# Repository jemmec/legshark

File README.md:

# legshark

An open source 60% (15 by 5) ortholinear keyboard designed with both flexability and familiarity in mind.

- Highly customizable 60% ortho layout
- "Plateless" o-ring mounting
- 3D printable case
- [UDB](https://github.com/Unified-Daughterboard/) Support

### Layout

The PCB supports many different layout options for the bottom row, embracing `1u` keys but also with some left and right `1.5u` modifier options.

The board also supports use of `2u` keys in the usual `TAB`, `LSHIFT`, `DELETE`, and `ENTER` locations to maintain familiarity and speed with these often used modifiers.

### PCB

> NOTE: It is recommended to use screw-in stabilizers (yes they work with o-ring) due to clip-ins sometimes slipping between the three holes in the bottom row. I have slightly reduced the clip-in hole size which has mitigated the issue, but made them quite hard to push in.

>_These images may not be up-to-date._

Supports the [Unified Daughterboard](https://github.com/Unified-Daughterboard/).

### Mounting Styles

Supports a unique "plateless" o-ring mounting style. The PCB also has through-holes for plate mounting should that be preferred.

#### "Plateless" o-ring plate

The "plateless" o-ring mounting style lets you enjoy the unique characteristics and sound of a platless + o-ring board with the added benefit of being able to remove/change the plate after soldering in the switches.

The printable plate files can be found in `./stls`. There are two files, one for `1.5u` spaced switches (pictured) and one for the `1u` spaced switches. Only the left side plate is supplied, you will need to vertically mirror the file in your slicer to print the right side. The optimal printing orientation is upside-down.

A standard 60% o-ring (OD 180-190mm) with a diameter of 2.5-3.5mm will work. 

>NOTE: If you intend to use a layout with the `2u` SHIFT or DELETE keys these plates may need modified in order to fit the stabs.

### Case

A 3D printable case designed around the "plateless" o-ring mounting system. It's a unibody design with a daughterboard cutout and recessed holes for 12mm rubber feet. The daughterboard is screwed into M2 threaded inserts.

Files for printing the case can be found in `./stls`. The print has been split into two parts, since it is too large for standard-sized printer volumes. The two halves are designed to be glued together using key and slot guides for alignment and added strength. The optimal printing orientation is vertically with the case-sides facing down.

>NOTE: I recommend using superglue to bond the two halves together.
>1) Glue all three keys into the slots of one of the halves. 
>2) Add glue along the mating surface and in the slots of the other half. 
>3) Carefully slide the two halves together using the keys and slots a guide. 
>4) Clamp the halves together and let the glue dry for 10-20 minutes.

### QMK

There is only one keymap avaliable for the keyboard currently. This keyboard has not been merged into the qmk repo yet. The firmware will need to be compiled and uploaded locally using [QMK](https://qmk.fm/). 

Copy `./qmk/keyboards` into your `/qmk_firmware` folder then run the following command to compile the firmware:
```
qmk compile -kb legshark/rev2 -km default
```

>NOTE: You will need to modify the keymaps to support different layouts!

### Keyboard Layout Editor:

```
[{x:2,c:"#c9a6de",t:"#383838",st:"KS-3-Tea",a:3,f:4},"ESC\n\n\n\n\n0\n\n\n\n\n\n0",{c:"#cccccc",a:1},"~\n`\n\n\n\n1\n\n\n\n\n\n0","!\n1\n\n\n\n2\n\n\n\n\n\n0","@\n2\n\n\n\n3\n\n\n\n\n\n0","#\n3\n\n\n\n4\n\n\n\n\n\n0","$\n4\n\n\n\n5\n\n\n\n\n\n0","%\n5\n\n\n\n6\n\n\n\n\n\n0","^\n6\n\n\n\n7\n\n\n\n\n\n0","&\n7\n\n\n\n8\n\n\n\n\n\n0","*\n8\n\n\n\n9\n\n\n\n\n\n0","(\n9\n\n\n\n10\n\n\n\n\n\n0",")\n0\n\n\n\n11\n\n\n\n\n\n0","_\n-\n\n\n\n12\n\n\n\n\n\n0","+\n=\n\n\n\n13\n\n\n\n\n\n0",{c:"#c9a6de",a:3},"DEL\n\n\n\n\n14\n\n\n\n\n\n0",{w:2},"DELETE\n\n\n\n2u\n0 14"],
[{w:2},"TAB\n\n\n\n2u\n1 0","\n\n\n\n\n0\n\n\n\n\n\n1","\n\n\n\n\n1\n\n\n\n\n\n1",{c:"#cccccc",f:6},"Q\n\n\n\n\n2\n\n\n\n\n\n1","W\n\n\n\n\n3\n\n\n\n\n\n1","E\n\n\n\n\n4\n\n\n\n\n\n1","R\n\n\n\n\n5\n\n\n\n\n\n1","T\n\n\n\n\n6\n\n\n\n\n\n1","Y\n\n\n\n\n7\n\n\n\n\n\n1","U\n\n\n\n\n8\n\n\n\n\n\n1","I\n\n\n\n\n9\n\n\n\n\n\n1","O\n\n\n\n\n10\n\n\n\n\n\n1","P\n\n\n\n\n11\n\n\n\n\n\n1",{a:1,f:4},"{\n[\n\n\n\n12\n\n\n\n\n\n1","}\n]\n\n\n\n13\n\n\n\n\n\n1","|\n\\\n\n\n\n14\n\n\n\n\n\n1"],
[{x:2,c:"#c9a6de",a:3},"CAPS\n\n\n\n\n0\n\n\n\n\n\n2","FN\n\n\n\n\n1\n\n\n\n\n\n2",{c:"#cccccc",f:6},"A\n\n\n\n\n2\n\n\n\n\n\n2","S\n\n\n\n\n3\n\n\n\n\n\n2","D\n\n\n\n\n4\n\n\n\n\n\n2",{a:1},"\n_\n\n\n\n5\nF\n\n\n\n\n2",{a:3},"G\n\n\n\n\n6\n\n\n\n\n\n2","H\n\n\n\n\n7\n\n\n\n\n\n2",{a:1},"\n_\n\n\n\n8\nJ\n\n\n\n\n2",{a:3},"K\n\n\n\n\n9\n\n\n\n\n\n2","L\n\n\n\n\n10\n\n\n\n\n\n2",{a:1,f:4},":\n;\n\n\n\n11\n\n\n\n\n\n2","\"\n'\n\n\n\n12\n\n\n\n\n\n2",{c:"#c9a6de",a:3},"\n\n\n\n\n13\n\n\n\n\n\n2","\n\n\n\n\n14\n\n\n\n\n\n2",{w:2},"ENTER\n\n\n\n2u\n2 14"],
[{w:2},"SHIFT\n\n\n\n2u\n3 0","\n\n\n\n\n0\n\n\n\n\n\n3","\n\n\n\n\n1\n\n\n\n\n\n3",{c:"#cccccc",f:6},"Z\n\n\n\n\n2\n\n\n\n\n\n3","X\n\n\n\n\n3\n\n\n\n\n\n3","C\n\n\n\n\n4\n\n\n\n\n\n3","V\n\n\n\n\n5\n\n\n\n\n\n3","B\n\n\n\n\n6\n\n\n\n\n\n3","N\n\n\n\n\n7\n\n\n\n\n\n3","M\n\n\n\n\n8\n\n\n\n\n\n3",{a:1,f:4},"<\n,\n\n\n\n9\n\n\n\n\n\n3",">\n.\n\n\n\n10\n\n\n\n\n\n3","?\n/\n\n\n\n11\n\n\n\n\n\n3",{c:"#bf6060",a:3,f:9},"↑\n\n\n\n\n12\n\n\n\n\n\n3",{c:"#c9a6de",f:4},"\n\n\n\n\n13\n\n\n\n\n\n3","\n\n\n\n\n14\n\n\n\n\n\n3"],
[{x:3,c:"#73c985"},"LCTL\n\n\n\n\n1\n\n\n\n\n\n4","\n\n\n\n\n2\n\n\n\n\n\n4","LALT\n\n\n\n\n3\n\n\n\n\n\n4",{c:"#7acdff",sm:"alps"},"\n\n\n\n\n4\n\n\n\n\n\n4","\n\n\n\n\n5\n\n\n\n\n\n4","\n\n\n\n\n6\n\n\n\n\n\n4","\n\n\n\n\n7\n\n\n\n\n\n4","\n\n\n\n\n8\n\n\n\n\n\n4","\n\n\n\n\n9\n\n\n\n\n\n4","\n\n\n\n\n10\n\n\n\n\n\n4",{c:"#bf6060",f:9},"←\n\n\n\n\n11\n\n\n\n\n\n4","↓\n\n\n\n\n12\n\n\n\n\n\n4","→\n\n\n\n\n13\n\n\n\n\n\n4"],
[{x:3,c:"#73c985",f:4,w:1.5},"LCTL\n\n\n\n\n4 1","\n\n\n\n\n2\n\n\n\n\n\n4",{w:1.5},"LALT\n\n\n\n\n4 4",{x:1,c:"#7acdff",w:3},"\n\n\n\n3u\n4 7",{x:1,c:"#73c985",w:1.5},"RALT\n\n\n\n\n4 10","\n\n\n\n\n4 12",{w:1.5},"RCTL\n\n\n\n\n4 13"],
[{x:3,w:1.5},"LCTL\n\n\n\n\n4 1",{w:1.5},"\n\n\n\n\n4 3",{c:"#7acdff",w:3},"\n\n\n\n3u\n4 5",{x:1,w:3},"\n\n\n\n3u\n4 9",{c:"#73c985",w:1.5},"\n\n\n\n\n4 11",{w:1.5},"RCTL\n\n\n\n\n4 13"],
[{x:8,c:"#7acdff",w:2},"\n\n\n\n2u\n4 7",{w:2},"\n\n\n\n2u\n4 8"],
[{x:7,w:2},"\n\n\n\n2u\n4 6",{w:2},"\n\n\n\n2u\n4 7"],
[{x:7,w:3},"\n\n\n\n3u\n4 6"],
[{x:9,w:3},"\n\n\n\n3u\n4 8"],
[{x:6,w:7},"\n\n\n\n7u\n4 7"]
```
# Liability

This open source hardware is provided as is and can not be held accountable for any damages and/or liabilities caused as a result of whatever you intend to use it for.

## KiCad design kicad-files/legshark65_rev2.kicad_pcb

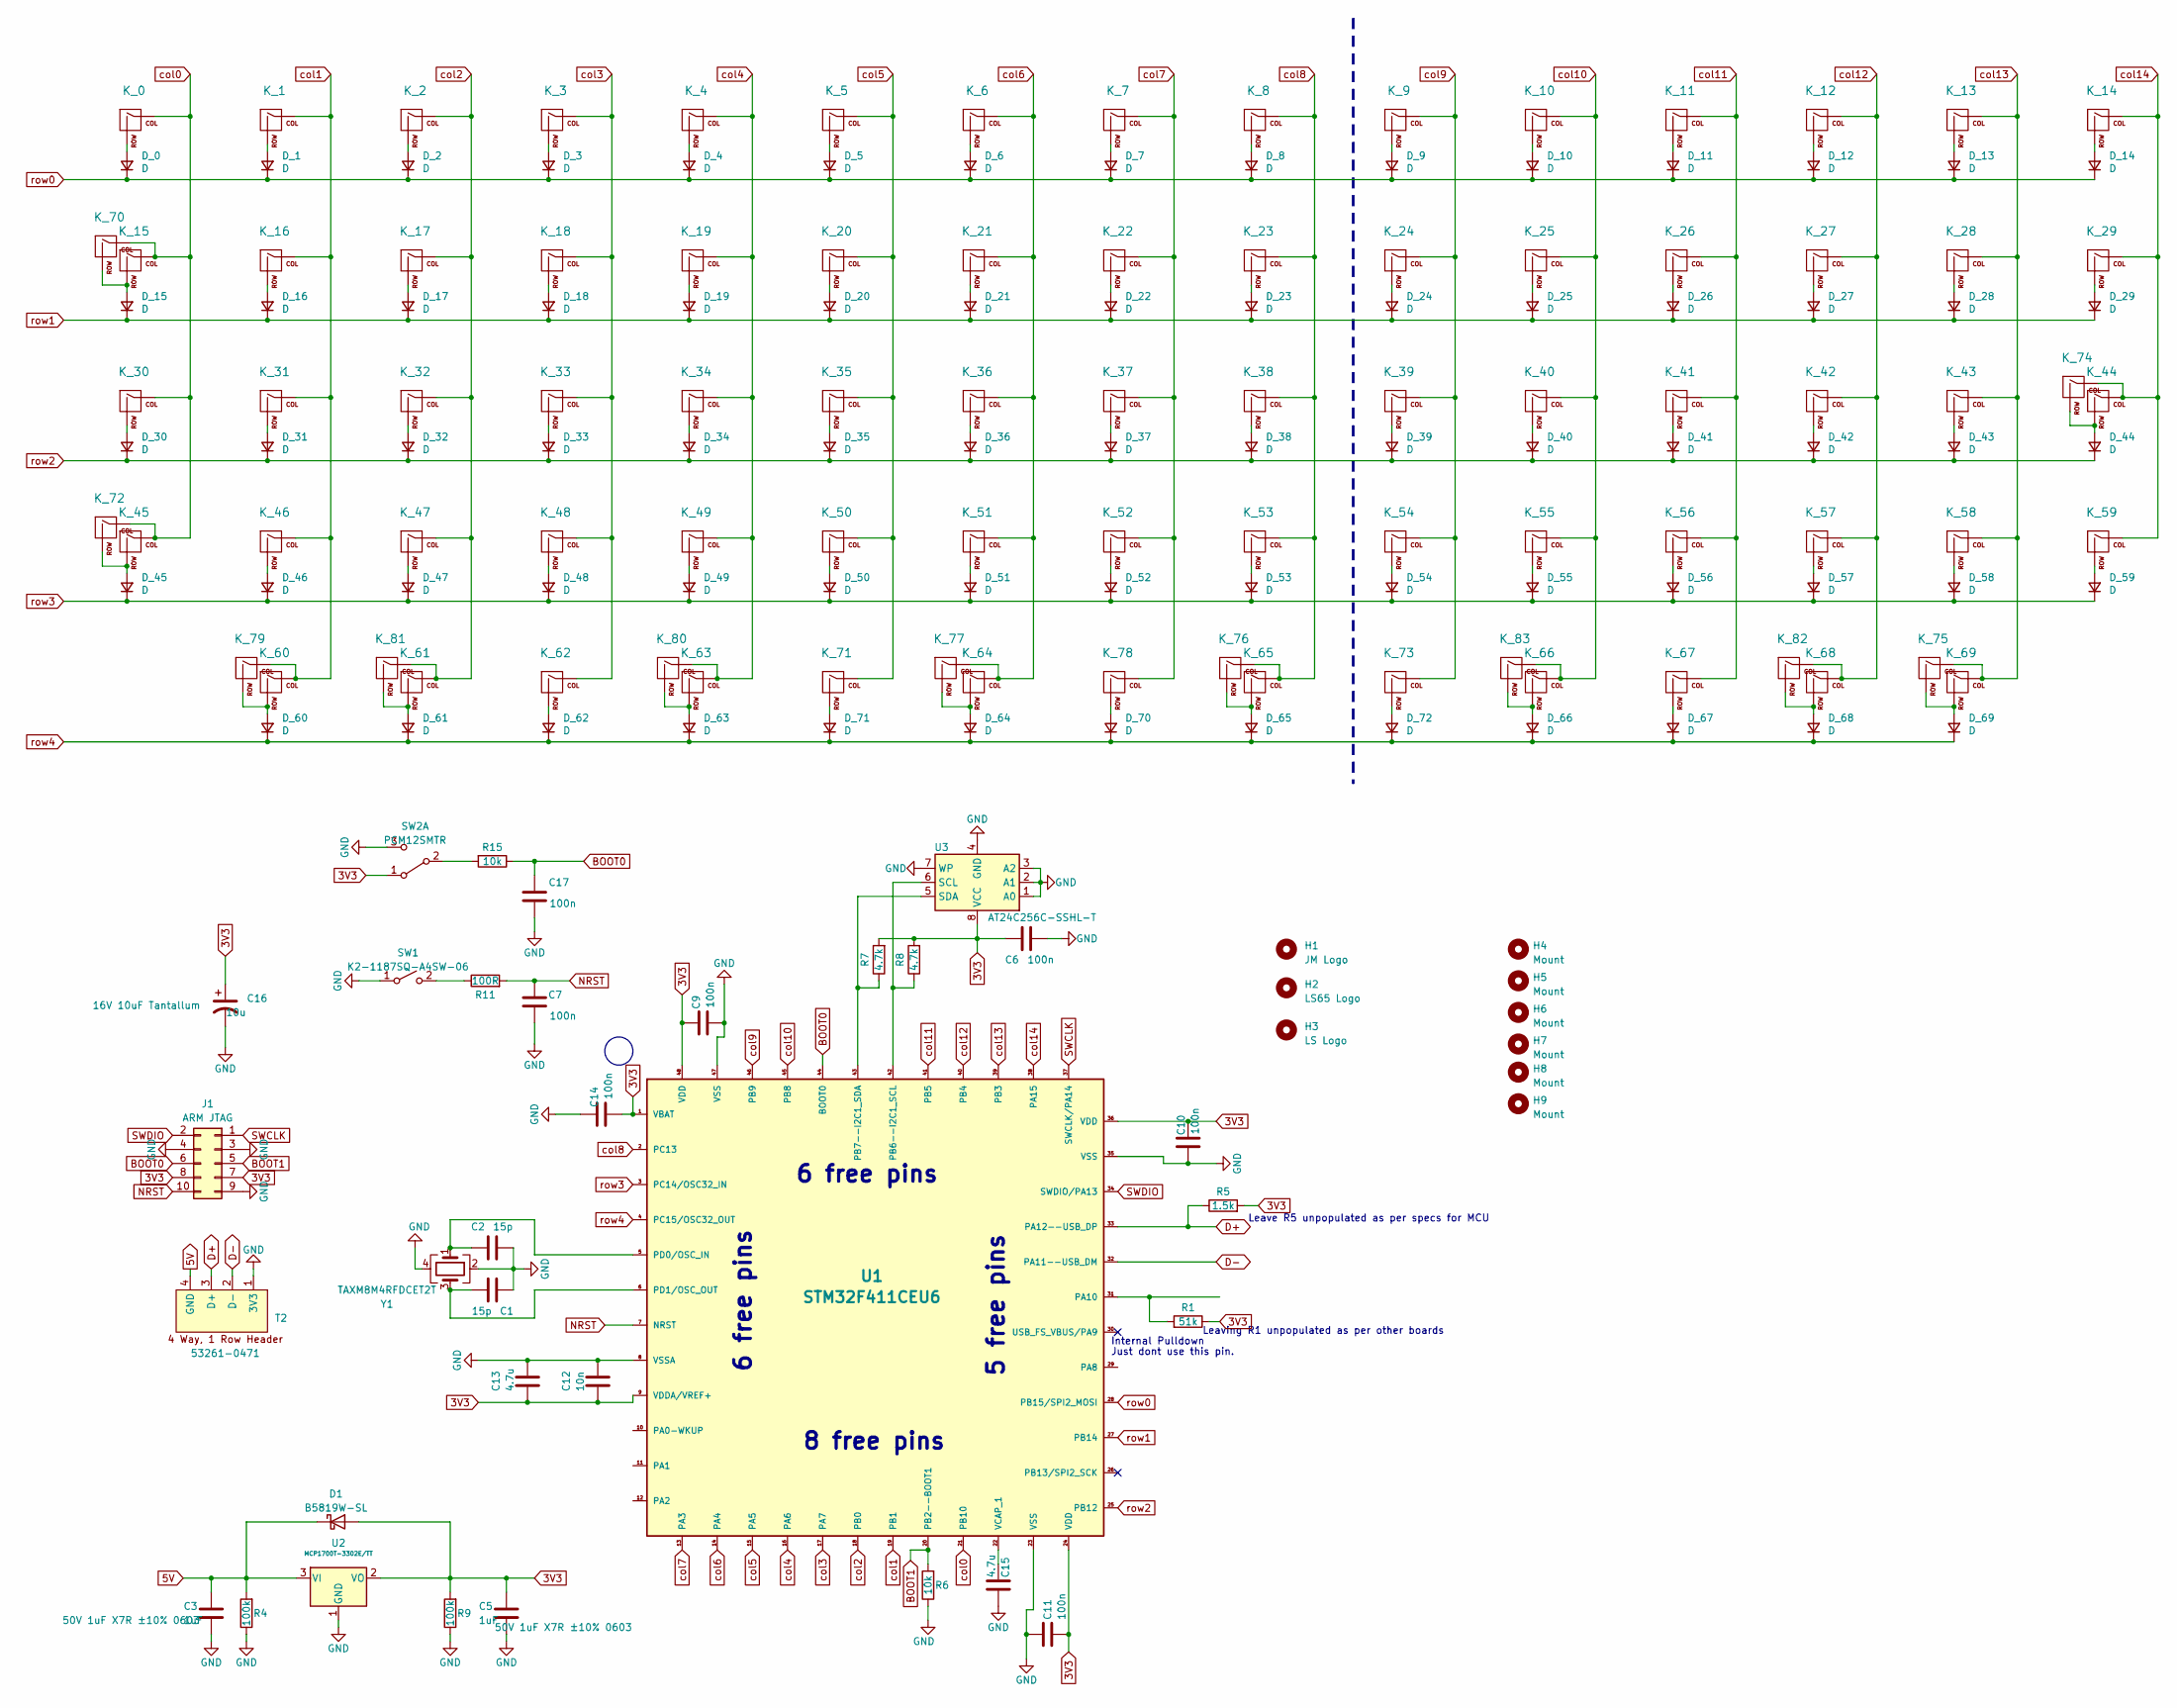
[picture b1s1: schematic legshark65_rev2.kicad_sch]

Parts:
C1, C2: 15p; C_0402_1005Metric_Pad0.74x0.62mm_HandSolder; Manufacturer Part Number CC0603JRNPO9BN150; LCSC Part C107037
C3, C5: 1uF; C_0402_1005Metric_Pad0.74x0.62mm_HandSolder; Manufacturer Part Number 0603B105K500NT
C6, C7, C9, C10, C11, C14, C17: 100n; C_0402_1005Metric_Pad0.74x0.62mm_HandSolder; Manufacturer Part Number CL10B104KB8NNNC; LCSC Part C1591
C12: 10n; C_0402_1005Metric_Pad0.74x0.62mm_HandSolder; Manufacturer Part Number CL10B103KB8NNNC; LCSC Part C1589
C13, C15: 4.7u; C_0402_1005Metric_Pad0.74x0.62mm_HandSolder; Manufacturer Part Number 0603X475M100NT; LCSC Part C108342
C16: 10u; CP_EIA-3216-10_Kemet-I_Pad1.58x1.35mm_HandSolder; Manufacturer Part Number TAJA106K016RNJ; LCSC Part C7171
D1: B5819W-SL; D_SOD-123
D_0, D_1, D_2, D_3, D_4, D_5, D_6, D_7, D_8, D_9, D_10, D_11, D_12, D_13, D_14, D_15, D_16, D_17, D_18, D_19, D_20, D_21, D_22, D_23, D_24, D_25, D_26, D_27, D_28, D_29, D_30, D_31, D_32, D_33, D_34, D_35, D_36, D_37, D_38, D_39, D_40, D_41, D_42, D_43, D_44, D_45, D_46, D_47, D_48, D_49, D_50, D_51, D_52, D_53, D_54, D_55, D_56, D_57, D_58, D_59, D_60, D_61, D_62, D_63, D_64, D_65, D_66, D_67, D_68, D_69, D_70, D_71, D_72: D; D_SOD-523
H1: JM Logo; jm_logo
H2: LS65 Logo; ls65_logo
H3: LS Logo; Legshark_Mask
H4, H5, H6, H7, H8, H9: Mount; MountingHole_3.2mm_M3_ISO14580
J1: ARM JTAG; PinHeader_2x5_P2.54mm_Vertical
K_0, K_1, K_2, K_3, K_4, K_5, K_6, K_7, K_8, K_9, K_10, K_11, K_12, K_13, K_14, K_15, K_16, K_17, K_18, K_19, K_20, K_21, K_22, K_23, K_24, K_25, K_26, K_27, K_28, K_29, K_30, K_31, K_32, K_33, K_34, K_35, K_36, K_37, K_38, K_39, K_40, K_41, K_42, K_43, K_44, K_45, K_46, K_47, K_48, K_49, K_50, K_51, K_52, K_53, K_54, K_55, K_56, K_57, K_58, K_59, K_60, K_61, K_62, K_63, K_66, K_67, K_68, K_69, K_71, K_73, K_81, K_82: KEYSW; MXOnly-1U-NoLED
K_64, K_76: KEYSW; MXOnly-2U-ReversedStabilizers-NoLED
K_65, K_77: KEYSW; MXOnly-3U-ReversedStabilizers-NoLED
K_70, K_72, K_74: KEYSW; MXOnly-2U-NoLED
K_75, K_79, K_80, K_83: KEYSW; MXOnly-1.5U-NoLED
K_78: KEYSW; Legshark_MXOnly-7U-3U-ReversedStabilizers-NoLED
R1: 51k; R_0402_1005Metric_Pad0.72x0.64mm_HandSolder
R4, R9: 100k; R_0402_1005Metric_Pad0.72x0.64mm_HandSolder
R5: 1.5k; R_0402_1005Metric_Pad0.72x0.64mm_HandSolder
R6, R15: 10k; R_0402_1005Metric_Pad0.72x0.64mm_HandSolder; Manufacturer Part Number 0603WAF1002T5E; LCSC Part C25804
R7, R8: 4.7k; R_0402_1005Metric_Pad0.72x0.64mm_HandSolder; Manufacturer Part Number 0603WAF4701T5E; LCSC Part C23162
R11: 100R; R_0402_1005Metric_Pad0.72x0.64mm_HandSolder; Manufacturer Part Number 0603WAF1000T5E; LCSC Part C22775
SW1: K2-1187SQ-A4SW-06; Manufacturer Part Number K2-1187SQ-A4SW-06; LCSC Part C92584
SW2: PCM12SMTR; Surface Mount Slide Switch SPDT; Manufacturer Part Number PCM12SMTR; LCSC Part C221841
T2: 53261-0471; Molex, PicoBlade, 53261, 4 Way, 1 Row, Right Angle PCB Head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
U1: STM32F411CEU6; STM_UFQFPN-48_LQFP-48-1EP_7x7mm_P0.5mm_HandSoldering; Manufacturer Part Number STM32F411; LCSC Part C60420
U2: MCP1700T-3302E/TT; SOT-23; Manufacturer Part Number MCP1700T-3302E/TT
U3: AT24C256C-SSHL-T; SOIC-8; Manufacturer Part Number AT24C256C-SSHL-T; LCSC Part C6482
Y1: TAXM8M4RFDCET2T; Crystal_SMD_3225-4Pin_3.2x2.5mm; Manufacturer Part Number TAXM8M4RFDCET2T; LCSC Part C403948

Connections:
3V3: C5.1, C6.1, C9.2, C10.2, C11.2, C12.2, C13.2, C14.1, C16.1, D1.2 (A), J1.7, J1.8, R1.1, R5.2, R7.2, R8.2, R9.2, SW2.1 (A), U1.1 (VBAT), U1.9 (VDDA/VREF+), U1.24 (VDD), U1.36 (VDD), U1.48 (VDD), U2.2 (VO), U3.8 (VCC)
5V: C3.1, D1.1 (K), R4.2, T2.4 (GND), U2.3 (VI)
BOOT0: C17.2, J1.6, R15.1, U1.44 (BOOT0)
BOOT1: J1.5, R6.2, U1.20 (PB2--BOOT1)
D+: R5.1, T2.3 (D+), U1.33 (PA12--USB_DP)
D-: T2.2 (D-), U1.32 (PA11--USB_DM)
GND: C1.1, C2.2, C3.2, C5.2, C6.2, C7.1, C9.1, C10.1, C11.1, C12.1, C13.1, C14.2, C15.2, C16.2, C17.1, J1.3, J1.4, J1.9, R4.1, R6.1, R9.1, SW1.1 (A), SW2.3 (C), T2.1 (3V3), U1.8 (VSSA), U1.23 (VSS), U1.35 (VSS), U1.47 (VSS), U2.1 (GND), U3.1 (A0), U3.2 (A1), U3.3 (A2), U3.4 (GND), U3.7 (WP), Y1.2, Y1.4
NRST: C7.2, J1.10, R11.2, U1.7 (NRST)
unnamed: D_0.2 (A), K_0.2 (ROW)
unnamed: D_1.2 (A), K_1.2 (ROW)
unnamed: D_2.2 (A), K_2.2 (ROW)
unnamed: D_3.2 (A), K_3.2 (ROW)
unnamed: D_4.2 (A), K_4.2 (ROW)
unnamed: D_5.2 (A), K_5.2 (ROW)
unnamed: D_6.2 (A), K_6.2 (ROW)
unnamed: D_7.2 (A), K_7.2 (ROW)
unnamed: D_8.2 (A), K_8.2 (ROW)
unnamed: D_9.2 (A), K_9.2 (ROW)
unnamed: D_10.2 (A), K_10.2 (ROW)
unnamed: D_11.2 (A), K_11.2 (ROW)
unnamed: D_12.2 (A), K_12.2 (ROW)
unnamed: D_13.2 (A), K_13.2 (ROW)
unnamed: D_14.2 (A), K_14.2 (ROW)
unnamed: D_15.2 (A), K_15.2 (ROW), K_70.2 (ROW)
unnamed: D_16.2 (A), K_16.2 (ROW)
unnamed: D_17.2 (A), K_17.2 (ROW)
unnamed: D_18.2 (A), K_18.2 (ROW)
unnamed: D_19.2 (A), K_19.2 (ROW)
unnamed: D_20.2 (A), K_20.2 (ROW)
unnamed: D_21.2 (A), K_21.2 (ROW)
unnamed: D_22.2 (A), K_22.2 (ROW)
unnamed: D_23.2 (A), K_23.2 (ROW)
unnamed: D_24.2 (A), K_24.2 (ROW)
unnamed: D_25.2 (A), K_25.2 (ROW)
unnamed: D_26.2 (A), K_26.2 (ROW)
unnamed: D_27.2 (A), K_27.2 (ROW)
unnamed: D_28.2 (A), K_28.2 (ROW)
unnamed: D_29.2 (A), K_29.2 (ROW)
unnamed: D_30.2 (A), K_30.2 (ROW)
unnamed: D_31.2 (A), K_31.2 (ROW)
unnamed: D_32.2 (A), K_32.2 (ROW)
unnamed: D_33.2 (A), K_33.2 (ROW)
unnamed: D_34.2 (A), K_34.2 (ROW)
unnamed: D_35.2 (A), K_35.2 (ROW)
unnamed: D_36.2 (A), K_36.2 (ROW)
unnamed: D_37.2 (A), K_37.2 (ROW)
unnamed: D_38.2 (A), K_38.2 (ROW)
unnamed: D_39.2 (A), K_39.2 (ROW)
unnamed: D_40.2 (A), K_40.2 (ROW)
unnamed: D_41.2 (A), K_41.2 (ROW)
unnamed: D_42.2 (A), K_42.2 (ROW)
unnamed: D_43.2 (A), K_43.2 (ROW)
unnamed: D_44.2 (A), K_44.2 (ROW), K_74.2 (ROW)
unnamed: D_45.2 (A), K_45.2 (ROW), K_72.2 (ROW)
unnamed: D_46.2 (A), K_46.2 (ROW)
unnamed: D_47.2 (A), K_47.2 (ROW)
unnamed: D_48.2 (A), K_48.2 (ROW)
unnamed: D_49.2 (A), K_49.2 (ROW)
unnamed: D_50.2 (A), K_50.2 (ROW)
unnamed: D_51.2 (A), K_51.2 (ROW)
unnamed: D_52.2 (A), K_52.2 (ROW)
unnamed: D_53.2 (A), K_53.2 (ROW)
unnamed: D_54.2 (A), K_54.2 (ROW)
unnamed: D_55.2 (A), K_55.2 (ROW)
unnamed: D_56.2 (A), K_56.2 (ROW)
unnamed: D_57.2 (A), K_57.2 (ROW)
unnamed: D_58.2 (A), K_58.2 (ROW)
unnamed: D_59.2 (A), K_59.2 (ROW)
unnamed: D_60.2 (A), K_60.2 (ROW), K_79.2 (ROW)
unnamed: D_61.2 (A), K_61.2 (ROW), K_81.2 (ROW)
unnamed: D_62.2 (A), K_62.2 (ROW)
unnamed: D_63.2 (A), K_63.2 (ROW), K_80.2 (ROW)
unnamed: D_64.2 (A), K_64.2 (ROW), K_77.2 (ROW)
unnamed: D_65.2 (A), K_65.2 (ROW), K_76.2 (ROW)
unnamed: D_66.2 (A), K_66.2 (ROW), K_83.2 (ROW)
unnamed: D_67.2 (A), K_67.2 (ROW)
unnamed: D_68.2 (A), K_68.2 (ROW), K_82.2 (ROW)
unnamed: D_69.2 (A), K_69.2 (ROW), K_75.2 (ROW)
unnamed: D_70.2 (A), K_78.2 (ROW)
unnamed: D_71.2 (A), K_71.2 (ROW)
unnamed: D_72.2 (A), K_73.2 (ROW)
unnamed: R11.1, SW1.2 (B)
unnamed: R15.2, SW2.2 (B)
unnamed: R1.2, U1.31 (PA10)
unnamed: R8.1, U1.42 (PB6--I2C1_SCL), U3.6 (SCL)
unnamed: R7.1, U1.43 (PB7--I2C1_SDA), U3.5 (SDA)
unnamed: C2.1, U1.5 (PD0/OSC_IN), Y1.1
unnamed: C1.2, U1.6 (PD1/OSC_OUT), Y1.3
unnamed: C15.1, U1.22 (VCAP_1)
SWCLK: J1.1, U1.37 (SWCLK/PA14)
SWDIO: J1.2, U1.34 (SWDIO/PA13)
col0: K_0.1 (COL), K_15.1 (COL), K_30.1 (COL), K_45.1 (COL), K_70.1 (COL), K_72.1 (COL), U1.21 (PB10)
col1: K_1.1 (COL), K_16.1 (COL), K_31.1 (COL), K_46.1 (COL), K_60.1 (COL), K_79.1 (COL), U1.19 (PB1)
col2: K_2.1 (COL), K_17.1 (COL), K_32.1 (COL), K_47.1 (COL), K_61.1 (COL), K_81.1 (COL), U1.18 (PB0)
col3: K_3.1 (COL), K_18.1 (COL), K_33.1 (COL), K_48.1 (COL), K_62.1 (COL), U1.17 (PA7)
col4: K_4.1 (COL), K_19.1 (COL), K_34.1 (COL), K_49.1 (COL), K_63.1 (COL), K_80.1 (COL), U1.16 (PA6)
col5: K_5.1 (COL), K_20.1 (COL), K_35.1 (COL), K_50.1 (COL), K_71.1 (COL), U1.15 (PA5)
col6: K_6.1 (COL), K_21.1 (COL), K_36.1 (COL), K_51.1 (COL), K_64.1 (COL), K_77.1 (COL), U1.14 (PA4)
col7: K_7.1 (COL), K_22.1 (COL), K_37.1 (COL), K_52.1 (COL), K_78.1 (COL), U1.13 (PA3)
col8: K_8.1 (COL), K_23.1 (COL), K_38.1 (COL), K_53.1 (COL), K_65.1 (COL), K_76.1 (COL), U1.2 (PC13)
col9: K_9.1 (COL), K_24.1 (COL), K_39.1 (COL), K_54.1 (COL), K_73.1 (COL), U1.46 (PB9)
col10: K_10.1 (COL), K_25.1 (COL), K_40.1 (COL), K_55.1 (COL), K_66.1 (COL), K_83.1 (COL), U1.45 (PB8)
col11: K_11.1 (COL), K_26.1 (COL), K_41.1 (COL), K_56.1 (COL), K_67.1 (COL), U1.41 (PB5)
col12: K_12.1 (COL), K_27.1 (COL), K_42.1 (COL), K_57.1 (COL), K_68.1 (COL), K_82.1 (COL), U1.40 (PB4)
col13: K_13.1 (COL), K_28.1 (COL), K_43.1 (COL), K_58.1 (COL), K_69.1 (COL), K_75.1 (COL), U1.39 (PB3)
col14: K_14.1 (COL), K_29.1 (COL), K_44.1 (COL), K_59.1 (COL), K_74.1 (COL), U1.38 (PA15)
row0: D_0.1 (K), D_1.1 (K), D_2.1 (K), D_3.1 (K), D_4.1 (K), D_5.1 (K), D_6.1 (K), D_7.1 (K), D_8.1 (K), D_9.1 (K), D_10.1 (K), D_11.1 (K), D_12.1 (K), D_13.1 (K), D_14.1 (K), U1.28 (PB15/SPI2_MOSI)
row1: D_15.1 (K), D_16.1 (K), D_17.1 (K), D_18.1 (K), D_19.1 (K), D_20.1 (K), D_21.1 (K), D_22.1 (K), D_23.1 (K), D_24.1 (K), D_25.1 (K), D_26.1 (K), D_27.1 (K), D_28.1 (K), D_29.1 (K), U1.27 (PB14)
row2: D_30.1 (K), D_31.1 (K), D_32.1 (K), D_33.1 (K), D_34.1 (K), D_35.1 (K), D_36.1 (K), D_37.1 (K), D_38.1 (K), D_39.1 (K), D_40.1 (K), D_41.1 (K), D_42.1 (K), D_43.1 (K), D_44.1 (K), U1.25 (PB12)
row3: D_45.1 (K), D_46.1 (K), D_47.1 (K), D_48.1 (K), D_49.1 (K), D_50.1 (K), D_51.1 (K), D_52.1 (K), D_53.1 (K), D_54.1 (K), D_55.1 (K), D_56.1 (K), D_57.1 (K), D_58.1 (K), D_59.1 (K), U1.3 (PC14/OSC32_IN)
row4: D_60.1 (K), D_61.1 (K), D_62.1 (K), D_63.1 (K), D_64.1 (K), D_65.1 (K), D_66.1 (K), D_67.1 (K), D_68.1 (K), D_69.1 (K), D_70.1 (K), D_71.1 (K), D_72.1 (K), U1.4 (PC15/OSC32_OUT)

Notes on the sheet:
6 free pins
5 free pins
Leave R5 unpopulated as per specs for MCU
Just dont use this pin.
Leaving R1 unpopulated as per other boards
8 free pins
Internal Pulldown

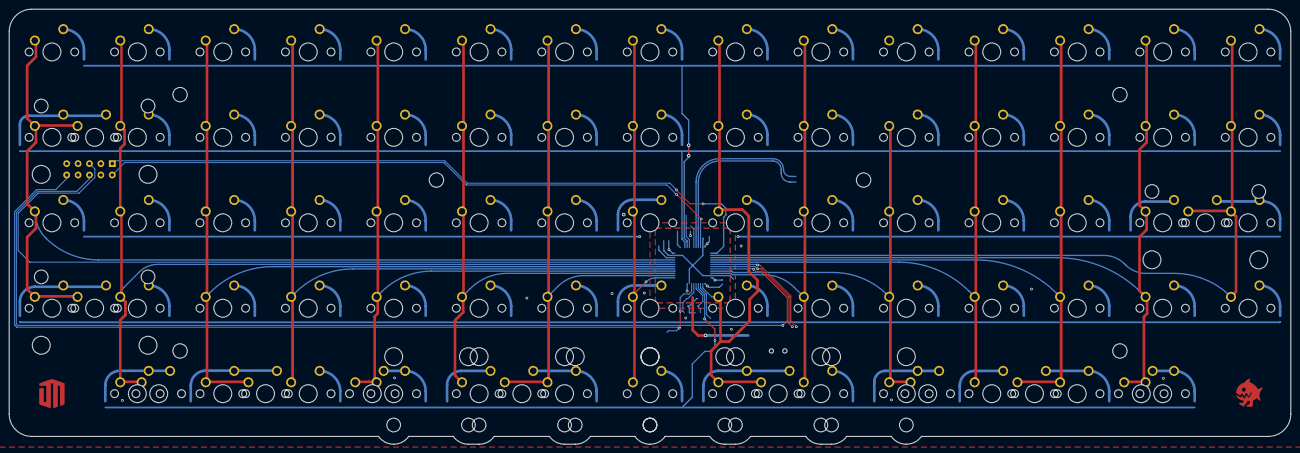
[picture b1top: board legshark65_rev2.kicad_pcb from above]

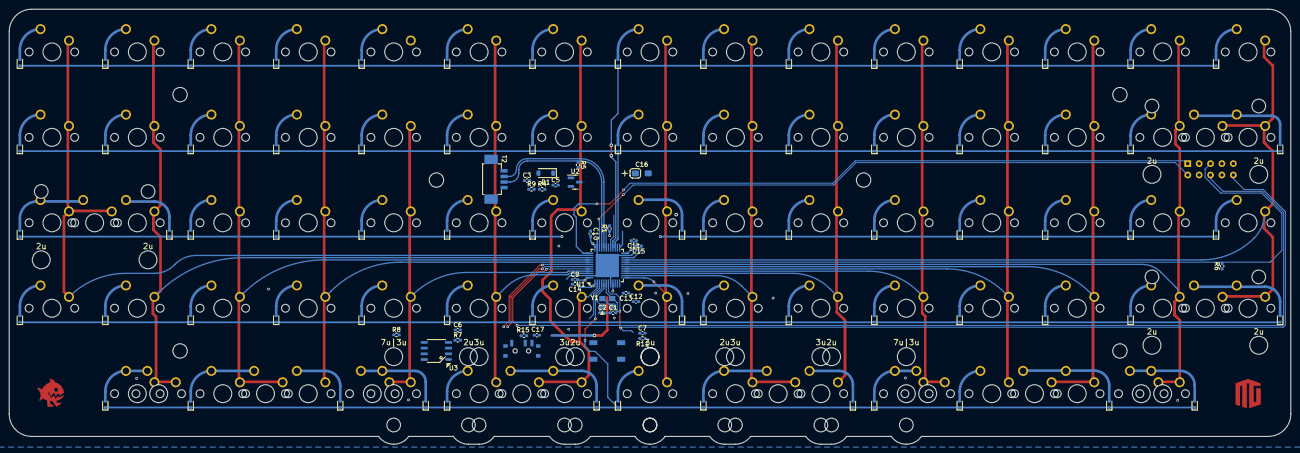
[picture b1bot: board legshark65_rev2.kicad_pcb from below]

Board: 2 copper layers, 285.8 x 97.0 mm, 199 parts (105 on the bottom side), 111 nets.

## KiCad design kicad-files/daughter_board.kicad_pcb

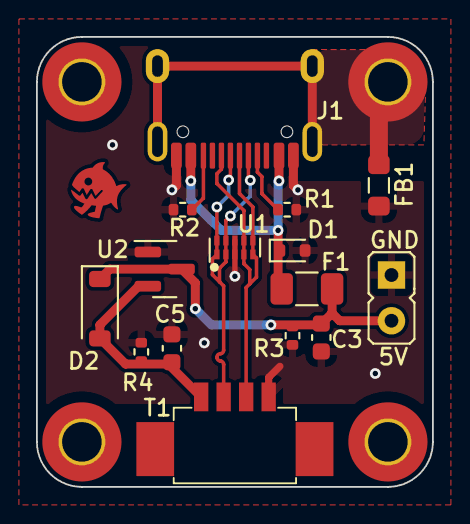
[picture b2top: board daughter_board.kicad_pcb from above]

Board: 2 copper layers, 22.0 x 25.0 mm, 20 parts (0 on the bottom side), 9 nets.

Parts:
C3, C5: 1uF; C_0603_1608Metric
D1: ESD5Z5V0; D_SOD-523
D2: B5819W-SL; D_SOD-123
F1: SMD0805-050-16V; Fuse_1206_3216Metric
FB1: GZ2012D601TF; L_0805_2012Metric_Pad1.05x1.20mm_HandSolder
H1: LegSharkLogo; Legshark_Small_Mask
J1: TYPE-C-31-M-12
J2: Conn_01x02; PinHeader_1x2_P2.54mm_Vertical
MH1, MH3, MH4: Mount-M2; MountingHole_2.2mm_M2_Pad_TopOnly
MH2: Mount-M2; MountingHole_2.2mm_M2_Pad_TopBottom
R1, R2: 5.1k; R_0402_1005Metric
R3, R4: 100k; R_0402_1005Metric
T1: 53261-0471; Molex, PicoBlade, 53261, 4 Way, 1 Row, Right Angle PCB Head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
U1: TPD4E05U06DQAR; USON-10_2.5x1.0mm_P0.5mm
U2: MCP1700T-3302E/TT; SOT-23

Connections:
3V3: C5.1, D2.2 (A), R4.2, T1.1 (3V3), U2.2 (VO)
5V: C3.1, D2.1 (K), F1.2, J2.2, R3.2, U2.3 (VI)
D+: J1.A6 (D+), J1.B6 (D+), T1.3 (D-), U1.4 (D2+), U1.5 (D2-), U1.6 (NC), U1.7 (NC)
D-: J1.A7 (D-), J1.B7 (D-), T1.2 (D+), U1.1 (IO1), U1.2 (IO2), U1.9 (NC), U1.10 (NC)
GND: C3.2, C5.2, D1.2 (A2), FB1.2, J1.A1 (GND), J1.B1 (GND), J2.1, R1.2, R2.2, R3.1, R4.1, T1.4 (GND), U1.3 (GND), U1.8 (GND), U2.1 (GND)
GNDPWR: FB1.1, J1.S (SHIELD), MH2.1
unnamed: J1.A5 (CC1), R1.1
unnamed: J1.B5 (CC2), R2.1
VBUS: D1.1 (A1), F1.1, J1.A4 (VBUS), J1.B4 (VBUS)

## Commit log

2023-04-29 Added git ignore
2023-04-29 Added layout
2023-04-29 Added version to readme
2023-04-29 Init kicad files from layout
2023-04-29 Change row and col name to r and c & added acheron libs
2023-04-29 Added STM32 micro controller to schematic
2023-04-29 Added Type C connector
2023-04-29 Renamed pins on STM
2023-04-29 Made outline
2023-04-30 Swapped switches to cherry MX only & Resized board
2023-04-30 Resized board again
2023-04-30 added measurement guides
2023-04-30 Moved Diodes for more practical spacing
2023-04-30 Hooked up the Type C connector
2023-04-30 Connected usb GNDPWR to inductor
2023-04-30 Connected the 3V3 regulator & ESD Protection
2023-04-30 Connected EEPROM to STM
2023-04-30 Rename row and col to use captial
2023-04-30 Added reset switch
2023-04-30 Added 3V3 connections to controller
2023-05-01 Placed reset switch & eeprom footprints
2023-05-01 Connected pulldown for 3V3 on the STM
2023-05-01 Connected EEPROM and RESET to STM
2023-05-01 Moved switch for better positioning
2023-05-01 Added connector for DB
2023-05-02 Added the cable header for DB to MB
2023-05-02 Added fill area for MB
2023-05-02 Connected all 3V3 to STM
2023-05-02 Started piecing together daughter board
2023-05-02 Finished ic placement for daughter board
2023-05-02 Straightened up the daughter board
2023-05-02 Completed wiring and zoning daughter board
2023-05-02 Added legshark logo to DB
2023-05-02 Rotated the molex header on the main board
2023-05-02 Resized MB again & started joining rows
2023-05-02 Added legshark logo back
2023-05-02 Started linking the front col
2023-05-02 Created Huge legshark logo
2023-05-03 Routed more of the connections
2023-05-03 Moved some diodes around
2023-05-03 Started naming the switches
2023-05-03 More naming and filleted edge
2023-05-05 Added more key name soldermask
2023-05-07 Added more labels
2023-05-07 Added more labels & Test wire columns
2023-05-07 Finished labelling all of the switches
2023-05-07 Moved the reset swtich
2023-05-07 Moved some devices further away from stab mount
2023-05-07 Added cut-outs around arrow keys and fixed boarder size
2023-05-07 Started re-routing the columns to be a lot more efficient
2023-05-07 Re-wired row traces to be straight lines
2023-05-07 Connected all of the columns
2023-05-07 Corrected sizing for the arrow key cutouts
2023-05-07 Connected all the rows
2023-05-07 Fixed unconnectd GND issues
2023-05-07 Fixed C0 not being curvy
2023-05-07 Moved some things around a little and added teardrops
2023-05-07 Made some more traces curvy
2023-05-08 Moved crystal closer to the MCU
2023-05-08 Started making USB lengths the same
2023-05-09 Matched USB D- and D+ trace length
2023-05-09 Fix distanc
2023-05-09 Added GND pad to the molex connector
2023-05-10 Swapped reset switch to less complicated SPDT switch
2023-05-10 Re connected the new reset functionality
2023-05-10 Moved resister further away from a MCU pin
2023-05-10 Updated schematic to be more readable
2023-05-10 Small change
2023-05-10 Fixed some 3v3 routing to be cleaner
2023-05-10 Routed the Columns along the bottom and connected to MCU
2023-05-10 Rejiggered row and col wires to avoid holes with new clearence settings
2023-05-10 Added no ground pour to USB data wires to aesthetics
2023-05-10 Added changed ground pour settings
2023-05-10 Moved some wires away from solder pads
2023-05-10 Swapped back to thermal reliefs beacuse I read the internet
2023-05-11 Added Serial Wire Debug header for CLK and DIO pins
2023-05-11 Updated molex header to be more accurate with better footprint
2023-05-11 Tweaked the 3v3 cable
2023-05-13 Removed cutouts
2023-05-14 Resize edge cut and removed fillet corners
2023-05-14 Re routed traces since cutouts are gone
2023-05-14 Updated to version 2 of the board layout
2023-05-15 Updated to version 2.1 (A true 65% keyboard (lol))
2023-05-15 Added macrolayout
2023-05-15 Added new kicad project for version 2 layout and coppied the MCU schematic
2023-05-15 Update schematic to noLED MX only footpints
2023-05-15 Updated PCB design constraints
2023-05-15 Connected most of the rows and cols
2023-05-15 Started adding 3v3 pour
2023-05-16 Created power pour on F and more wiring completion
2023-05-16 Started connecting cols
2023-05-17 Connected all of the wires of the new board
2023-05-17 Lost of small changes to board
2023-05-17 Finished wiring the board
2023-05-18 Added names to molex connector
2023-05-18 Lost of small changes
2023-05-18 Added daughter board project files
2023-05-18 Added components to the daughter board
2023-05-18 SMall changes to the db
2023-05-21 Fixed up the daughter board
2023-05-21 Finished daughter board
2023-05-21 Fixed the boards edge cuts
2023-05-22 Fixing up the schematic's of daughter and mother boards
2023-05-22 More small tweaks to the daughter boardd
2023-05-22 Small changes to motherboard
2023-05-22 More minor clearance changes
2023-05-22 Added some front graphics to the motherboard pcb
2023-05-24 Added legshark logo to the daugherboard
2023-05-24 Added parts
2023-05-24 Finished adding parts to the daughter board
2023-05-24 Filling out the BOM of the motherboard
2023-05-24 Finished add BOM to motherboard & fixing some small parts
2023-05-24 Added header for 5V on daughter board and updated BOM a little
2023-05-24 Updated small things on daughter board bom
2023-05-25 Lots of small routing and quality changes to the motherboard
2023-05-31 Made the board's edge cut slightly smaller
2023-05-31 Moved logos up a little
2023-06-04 Tweaked layout a little bit and updated to version 2.2
2023-06-04 Updated PCB and schematic to v2.2 layout
2023-06-04 Made some very slight changes as per processing
2023-06-20 Added inital firmware version backup
2023-06-21 Added dfx for laser cutting a plate
2023-06-21 Added 0.5mm tol plate
2023-07-02 Moved the branding and JTAG to be positioned more between the switches
2023-07-02 Small change to pcb
2023-07-05 Updated qmk firmware to include function layer
2023-07-11 Updated readme with the rev2 layout
2023-07-11 fixed typo in readme
2023-07-16 Removed the rev2 stuff from the readme
2023-07-20 Updated readme with Revision 2 design
2023-07-23 Started creating the revision 2 board
2023-07-23 Added the 7u spacebar and extra
2023-07-23 Finished placing the extra keys
2023-07-23 Updated readme with correct and complete layout
2023-07-23 Made diodes small and fixed some connections
2023-07-23 Fixed layout image res
2023-07-23 Added inital tabs for the bottom stabs
2023-07-23 Started routing the switches
2023-07-24 Added ground fill
2023-07-24 Added the 5V to 3V3 stepdown schematic from db to the mb
2023-07-24 Made more connections
2023-07-24 More routing
2023-07-25 Ripped up traces and started placing io
2023-07-25 Updated layout in readme
2023-07-25 Added alternate mods to the right side
2023-07-25 Removed the labels from common diodes
2023-07-25 Added 3U stabs to the 7U footprint for even more layout support
2023-07-26 Added power rail
2023-07-26 Changed board settings'
2023-07-26 added mounting holes with clearence
2023-07-26 Starting to come up with ways mount the board
2023-07-26 More thinking
2023-07-26 Started adding all of the components onto the board
2023-07-26 Started running some test routes
2023-07-26 Added more routing and planning
2023-07-27 Started connecting more stuff
2023-07-27 Started routing NRST BOOT0 BOOT1 etc
2023-07-27 Moved the JTAG and routed NRST and BOOT0 to it
2023-07-27 Route swdo swidioidaod
2023-07-27 Started routing cols
2023-07-27 routed the hard wire through the MCU
2023-07-27 Made the pours correct distance
2023-07-27 Added connections to col and row
2023-07-28 Connected the RST EEPROM BOOT devices
2023-07-30 Locked the finished devices
2023-07-30 Routed the 5v to 3.3v step down
2023-07-30 Lots of small changes all over the board changes most of the wires down to 0.4mm instead of 0.6
2023-07-30 Started thinking about the mounting possibilities
2023-07-30 Conceptualizing mounting ideas
2023-07-30 Added cutouts to sides and changed mounting ideas again
2023-07-30 Added VIA ground stiching across the bored
2023-07-30 Added soldermask border
2023-07-30 Moved some diodes from the edge
2023-07-30 fixed board
2023-07-31 Made the mounting holes sold connection to gnd
2023-07-31 Some small change i am not sure
2023-07-31 Making the tracks have a more consistant width
2023-07-31 Made the tacks thicker and aligned some refs
2023-07-31 Added leg shark logo to the silkscreen
2023-07-31 Added outline legshark logo
2023-08-01 Added plus and minus to the CAPS LED
2023-08-01 Added indicator for the JTAG
2023-08-01 Made some schematic text more readable
2023-08-01 Added some more comments to schematic
2023-08-01 Added rev2 inital plate
2023-08-01 Added plate with correct stab rotation
2023-08-02 Small changes
2023-08-06 Re made the mounting solution and cleaned up the boards edgs
2023-08-06 Added 2u key option instead of DEL
2023-08-06 Updating board graphics
2023-08-06 Added legshark logo silkscreen front
2023-08-09 Updated readme with final layout and matrix
2023-08-09 Fixed KLE a little
2023-08-09 Updated spacing in image a little
2023-08-09 Added extra 1.5 and cut out the corners
2023-08-09 Updated KLE and Image
2023-08-09 Added more comments on the board, switch indicators etc
2023-08-09 More graphics
2023-08-10 Added more silkscreen comments
2023-08-10 Graphics'
2023-08-16 Added EZMate connector and optional JST pads
2023-08-16 Added QR code
2023-08-16 Moved some graphics around and made some wires more aesthetic
2023-08-17 Finalized the front silkscreen graphics
2023-08-20 Moved the bottom screw holes up by 1mm to account for the outer 1.5u switch
2023-08-20 Added wired option and some minor changes
2023-08-20 Added JTAG reference to silkscreen
2023-08-20 Added better less broken silkscreen graphic
2023-08-20 I should probably go to sleep now
2023-08-21 Finally happy with the graphics
2023-08-21 Some small adjustments to the graphics
2023-08-21 Added a front and back pcb image
2023-08-22 Cleaning up the readme
2023-08-22 Added more graphics and fixed some small DRC things
2023-08-22 Moved position of wired and JST connectors
2023-08-22 Moved some via around
2023-08-23 Some small tweaks to make it better of course
2023-08-23 Moved the bottom plate mounts up 1 unit
2023-09-17 Update gitignore
2023-09-17 Added power indicator LED
2023-11-01 Made the silk screen a little bit more readable
2023-11-01 Added bigger cutouts and deciding what to do with stab mounts
2023-11-03 Changes stab hole size to be a bit tighter
2023-11-03 Went all out and added more 2u options because im insane
2023-11-03 Change cutout holes size a little again
2023-12-31 Some minor tweaks
2024-01-01 Started updating the BOM
2024-01-02 Finished BOM basically
2024-01-05 Ignore .lck and many small changed to pcb
2024-01-05 Move JST over to give room for connector
2024-01-05 Even wires
2024-01-05 Slightly better silk screen indicator
2024-01-05 Add jtag ref thing
2024-01-05 Add many components to DNP
2024-01-08 Got C13 C12 ref mixed up
2024-01-27 Added rev2 qmk firmware
2024-01-29 added capslock to config
2024-01-29 Small bug with qmk config
2024-02-08 changed qmk folder name to be just legshark
2024-02-08 Added macro for fun to keymap
2024-02-08 Added more macros
2024-04-16 Update readme again
2024-04-16 More readme updating
2024-04-16 Added stl files
2024-04-16 Added title img
